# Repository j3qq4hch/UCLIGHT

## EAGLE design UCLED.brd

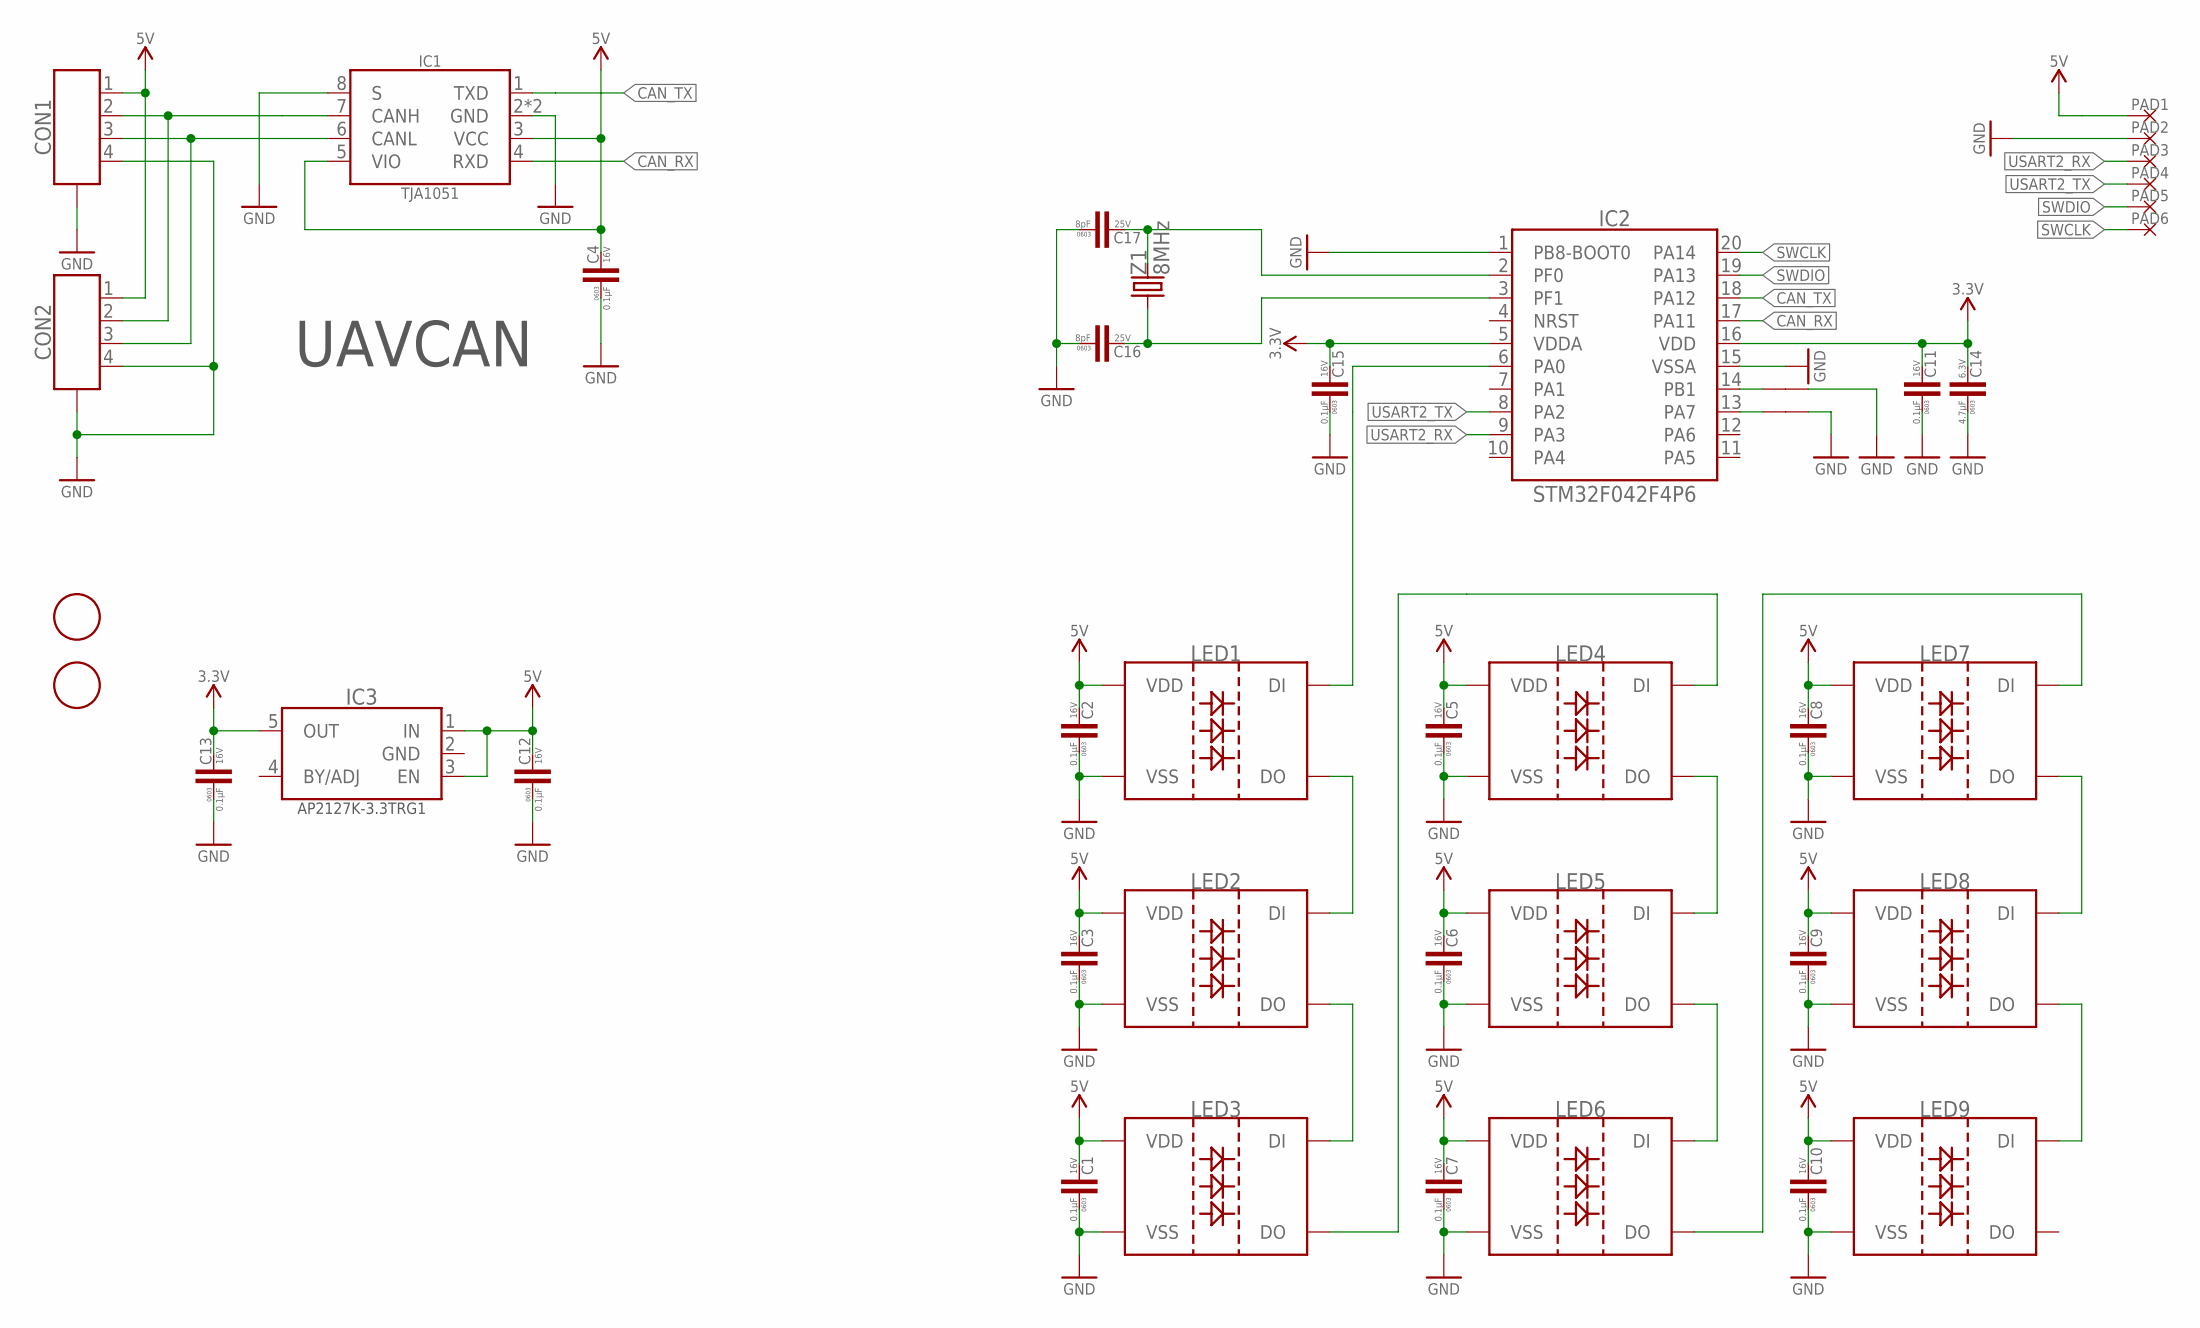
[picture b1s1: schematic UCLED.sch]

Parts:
C1, C2, C3, C4, C5, C6, C7, C8, C9, C10, C11, C12, C13, C15: 0.1µF; C0603
C14: 4.7µF; C0603
C16, C17: 8pF; C0603
CON1, CON2: CON-4P-TABS-JST_GH-RA; JST_GH-4P-RA
FD1, FD2: FIDUCIALMOUNT; FIDUCIA-MOUNT
IC1: TJA1051; SOT782-1
IC2: STM32F042F4PX; TSSOP20; DIGIKEY# 497-17343-ND
IC3: AP2127-3.3; SOT23-5
J1, J2: CONNECTION
LED1, LED2, LED3, LED4, LED5, LED6, LED7, LED8, LED9: WS2812B
PAD1, PAD2, PAD3, PAD4, PAD5, PAD6: PAD-S_2X2; 2х2
Z1: 8MHz; NX3225GD

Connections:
CAN_RX: IC1.4 (RXD), IC2.17 (PA11)
CAN_TX: IC1.1 (TXD), IC2.18 (PA12)
GND: C1.P$1 (1), C2.P$1 (1), C3.P$1 (1), C4.P$1 (1), C5.P$1 (1), C6.P$1 (1), C7.P$1 (1), C8.P$1 (1), C9.P$1 (1), C10.P$1 (1), C11.P$1 (1), C12.P$1 (1), C13.P$1 (1), C14.P$1 (1), C15.P$1 (1), C16.P$1 (1), C17.P$1 (1), CON1.4, CON1.M$0 (GND), CON1.M$1 (GND), CON2.4, CON2.M$0 (GND), CON2.M$1 (GND), IC1.2 (GND), IC1.8 (S), IC1.PAD (GND), IC2.1 (PB8-BOOT0), IC2.15 (VSSA), IC3.2 (GND), J1.P$2, J2.P$2, LED1.3 (VSS), LED2.3 (VSS), LED3.3 (VSS), LED4.3 (VSS), LED5.3 (VSS), LED6.3 (VSS), LED7.3 (VSS), LED8.3 (VSS), LED9.3 (VSS), PAD2.P$1
unnamed: IC2.6 (PA0), LED1.4 (DI)
unnamed: LED1.2 (DO), LED2.4 (DI)
unnamed: LED2.2 (DO), LED3.4 (DI)
unnamed: LED3.2 (DO), LED4.4 (DI)
unnamed: LED4.2 (DO), LED5.4 (DI)
unnamed: LED5.2 (DO), LED6.4 (DI)
unnamed: LED6.2 (DO), LED7.4 (DI)
unnamed: LED7.2 (DO), LED8.4 (DI)
unnamed: LED8.2 (DO), LED9.4 (DI)
unnamed: IC2.14 (PB1), J1.P$1
unnamed: IC2.13 (PA7), J2.P$1
unnamed: C17.P$2 (2), IC2.2 (PF0), Z1.2
unnamed: C16.P$2 (2), IC2.3 (PF1), Z1.1
unnamed: CON1.2, CON2.2, IC1.7 (CANH)
unnamed: CON1.3, CON2.3, IC1.6 (CANL)
SWCLK: IC2.20 (PA14), PAD6.P$1
SWDIO: IC2.19 (PA13), PAD5.P$1
USART2_RX: IC2.9 (PA3), PAD3.P$1
USART2_TX: IC2.8 (PA2), PAD4.P$1
VDD_3V3: C11.P$2 (2), C13.P$2 (2), C14.P$2 (2), C15.P$2 (2), IC2.5 (VDDA), IC2.16 (VDD), IC3.5 (OUT)
VDD_5V: C1.P$2 (2), C2.P$2 (2), C3.P$2 (2), C4.P$2 (2), C5.P$2 (2), C6.P$2 (2), C7.P$2 (2), C8.P$2 (2), C9.P$2 (2), C10.P$2 (2), C12.P$2 (2), CON1.1, CON2.1, IC1.3 (VCC), IC1.5 (VIO), IC3.1 (IN), IC3.3 (EN), LED1.1 (VDD), LED2.1 (VDD), LED3.1 (VDD), LED4.1 (VDD), LED5.1 (VDD), LED6.1 (VDD), LED7.1 (VDD), LED8.1 (VDD), LED9.1 (VDD), PAD1.P$1

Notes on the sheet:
UAVCAN

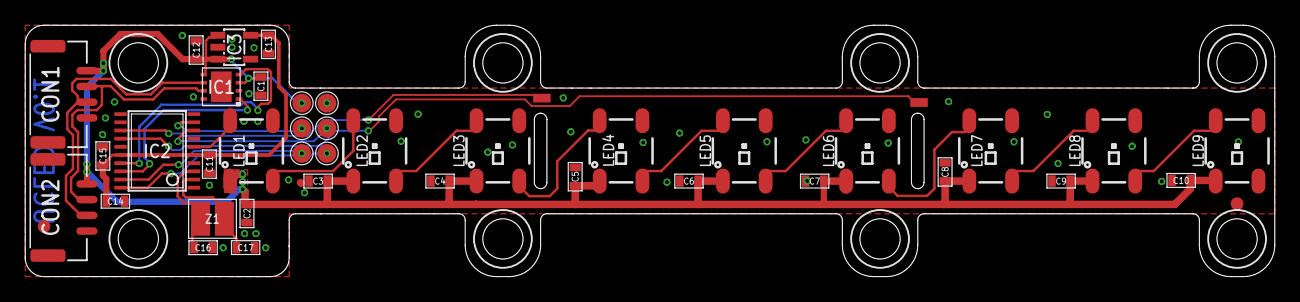
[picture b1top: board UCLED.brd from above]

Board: 2 copper layers, 99.4 x 20.0 mm, 44 parts (2 on the bottom side), 24 nets.

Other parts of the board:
U$2: DRAGON-30X13
U$3: ZUBAX_20X9

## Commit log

2019-03-09 initial import
2019-03-11 proper gitignore
2019-03-26 V0.1 completed
2019-03-26 attribute fixes
2019-03-26 manufacturing docs
